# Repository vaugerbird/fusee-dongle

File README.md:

# HOPEFULLY THIS WARNING IS BIG ENOUGH!
**DO NOT use this repository as it stands!!! I still have much to work on, I just made it public in case there was anybody that wanted to see what I'm doing or help out**

# fusee-dongle
A single PCB fusee injector dongle based around the Atmel SAMD21. Based on my [sam fusee launcher](https://github.com/vaugerbird/sam-fusee-launcher) project, which is based on [sam fusee launcher](https://github.com/noemu/sam-fusee-launcher). This project uses a modified version of main.ino from [electronrancher's SAMD_Fusee_Multiloader](https://github.com/electronrancher/SAMD_Fusee_Multiloader) to allow multiple for payloads.

## Standard disclaimer
This project was created only for educational purposes, and does not enable any kind of copyright infringement. Seriously, don't use this project for anything illegal, I don't need or want the Ninty ninjas coming after me.

# Build and Install
### Create/Update the Payload
* Download your favorite payload(s) from its appropriate repository(s)
* Run the python script in the `tools` folder, using the appropriate converter for your payload, with this command, replacing the path with your own:
`python binConverterPayload.py "C:\pathToMyPayload\payloadName.bin"`, or just drag the .bin file on the script to automatically add the path
* In the same folder as the .bin file is located, a new .h file should appear. Make sure the new file is named `hekate.h`, `fusee.h`, and `package3.h`. Copy the new file to the `main` folder and choose to replace the old file

### Install Board to IDE
* Download and install arduino IDE http://www.arduino.cc/en/Main/Software
* In Arduino: go to "Preferences" and add to "Additional Board Manager URLs" following URL:  `custom board definition coming soon`
* Go to "Tools > Board > Board Manager" and select "Type: All" and
* Input "Fusee Dongle" in the search box
* Install "SAMD Fusee Dongle"
* Select the dongle with "Tools > Board > SAMD Fusee Dongle"

### IDE Setup
* Go to "Sketch > Include Library > Manage Libraries" and install USBHost and FlashStorage
* Connect the dongle to your computer and double click the reset button
* Go to "Tools > Port" and select your connected dongle. (If the name does not show up, use Device Manager to find the proper COM port)
* Download this repository, open main/main.ino with Arduino IDE

### Usage
* When the LED is blinking blue, plug the dongle in and the payload should inject automatically
* To change the payload, press the leftmost button once to advance the payload, and press the rightmost one to confirm the selected payload.
* If you want to inject again, press the middle button and the light should start blinking blue again

Status LED meanings:
* 1 blink blue -> searching for Switch, injecting payload 1
* 2 blinks blue -> searching for Switch, injecting payload 2
* 3 blinks blue -> searching for Switch, injecting payload 3
* Red -> no Switch found
* Solid green, then off (except the power LED) -> finished successfully

# Thanks to:
* [electronrancher](https://github.com/electronrancher)
* [noemu](https://github.com/noemu/sam-fusee-launcher)
* [atlas44](https://github.com/atlas44/sam-fusee-launcher)
* [CTCaer](https://github.com/CTCaer/hekate)
* [SciresM](https://github.com/SciresM)
* And the rest of the community!

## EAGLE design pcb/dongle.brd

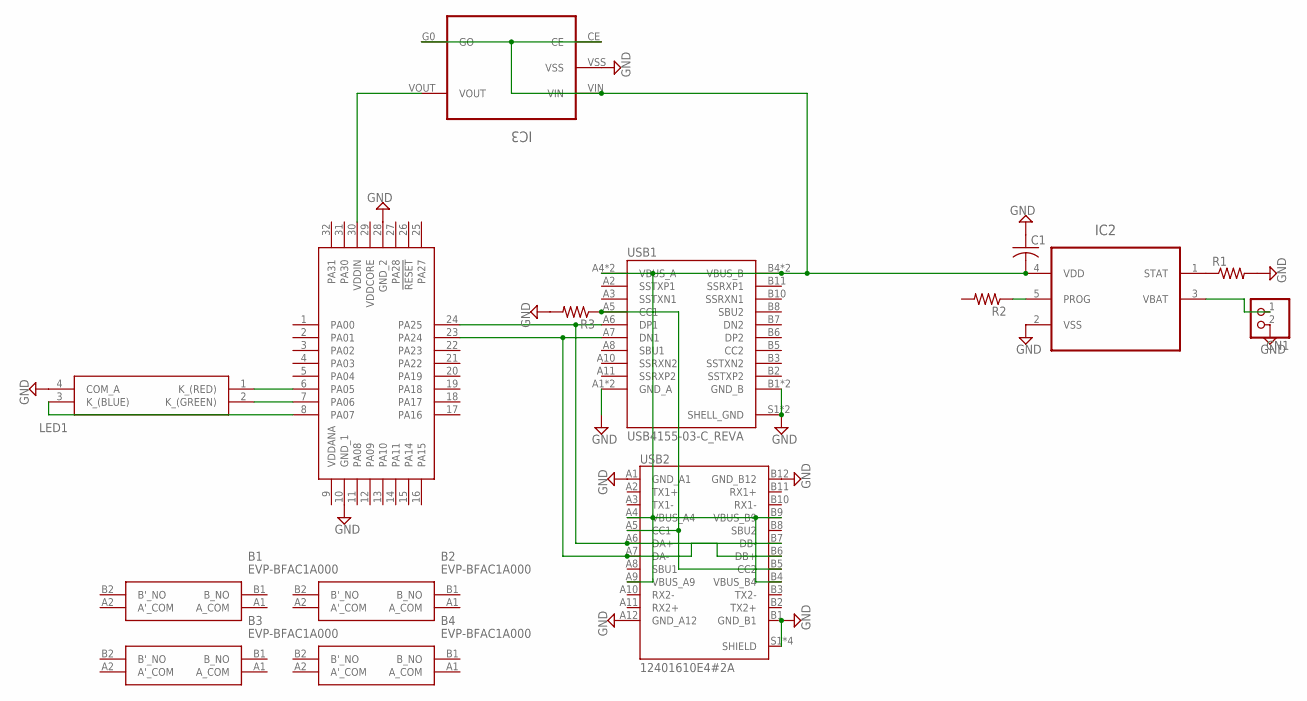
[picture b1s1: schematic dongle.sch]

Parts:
B1, B2, B3, B4: EVP-BFAC1A000; EVPBFAC1A000
C1: C-USC0805; C0805
CN1: JST_2PIN-SMT-RA; JST-PH-2-SMT-RA
IC1: ATSAMD21E18A-AFT; QFP80P900X900X120-32N
IC2: MCP73831T-2ACI/OT; SOT95P280X145-5N
IC3: IC_XC8107AC20MR-G
LED1: ASMB-MTB1-0B3A2; ASMBMTB10B3A2
R1, R2, R3: R-US_R0805; R0805
USB1: USB4155-03-C_REVA; GCT_USB4155-03-C_REVA
USB2: 12401610E4#2A; AMPHENOL_12401610E4#2A

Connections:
3.3V: IC1.30 (VDDIN), IC3.VOUT
3.3VBAT: CN1.1 (2), IC2.3 (VBAT)
5VIN: C1.2, IC2.4 (VDD), IC3.CE, IC3.G0 (GO), IC3.VIN, USB1.A4 (VBUS_A), USB1.A9 (VBUS_A), USB1.B4 (VBUS_B), USB1.B9 (VBUS_B), USB2.A4 (VBUS_A4), USB2.A9 (VBUS_A9), USB2.B4 (VBUS_B4), USB2.B9 (VBUS_B9)
B: IC1.8 (PA07), LED1.3 (K_(BLUE))
CC: R3.1, USB1.A5 (CC1), USB2.A5 (CC1), USB2.B5 (CC2)
D+: IC1.24 (PA25), USB1.A6 (DP1), USB2.A6 (DA+), USB2.B6 (DB+)
D-: IC1.23 (PA24), USB1.A7 (DN1), USB2.A7 (DA-), USB2.B7 (DB-)
G: IC1.7 (PA06), LED1.2 (K_(GREEN))
GND: C1.1, CN1.2 (1), IC1.10 (GND_1), IC1.28 (GND_2), IC2.2 (VSS), IC3.VSS, LED1.4 (COM_A), R1.2, R3.2, USB1.A1 (GND_A), USB1.A12 (GND_A), USB1.B1 (GND_B), USB1.B12 (GND_B), USB1.S1 (SHELL_GND), USB1.S2 (SHELL_GND), USB2.A1 (GND_A1), USB2.A12 (GND_A12), USB2.B1 (GND_B1), USB2.B12 (GND_B12), USB2.S1 (SHIELD), USB2.S2 (SHIELD), USB2.S3 (SHIELD), USB2.S4 (SHIELD)
PROG: IC2.5 (PROG), R2.1
R: IC1.6 (PA05), LED1.1 (K_(RED))
STAT: IC2.1 (STAT), R1.1

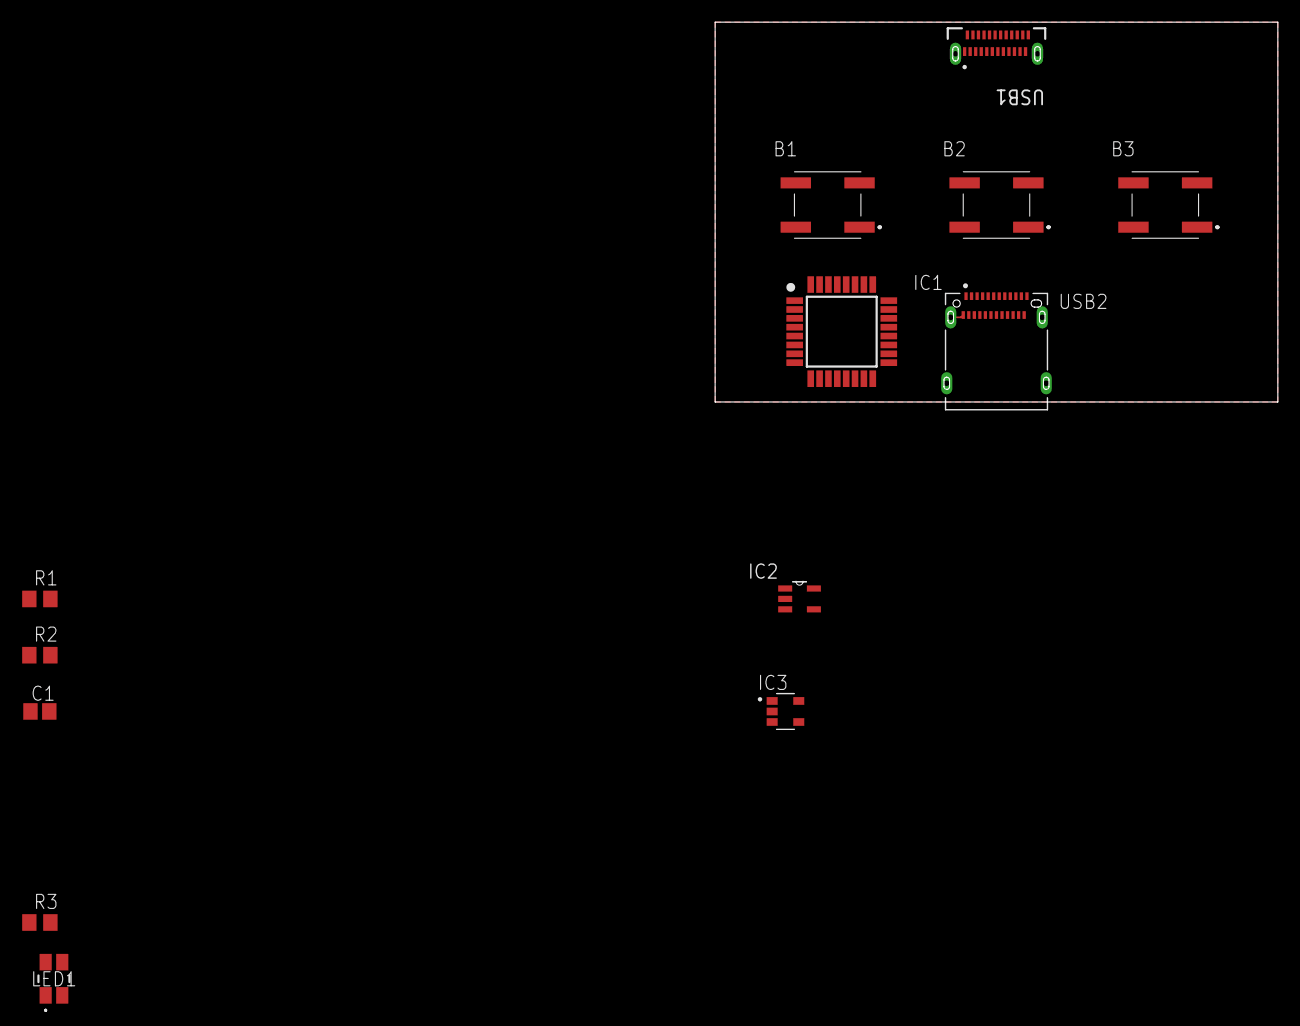
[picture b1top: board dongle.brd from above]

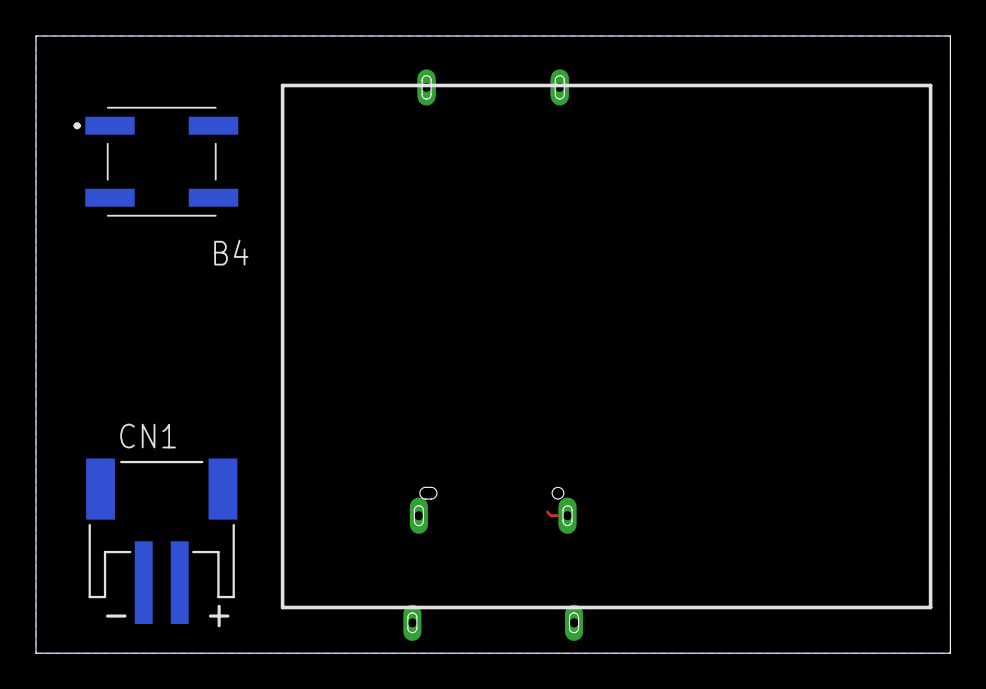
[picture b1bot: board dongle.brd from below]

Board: 2 copper layers, 50.8 x 34.3 mm, 15 parts (2 on the bottom side), 12 nets.

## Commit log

2021-11-01 Create LICENSE
2021-11-02 Add starting files
2021-11-03 Lots of all around work on the code and board
2021-11-13 Changed some parts sources and worked on board
